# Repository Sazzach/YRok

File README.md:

## Building

To build the firmware, first download the GNU ARM toolchain from: https://developer.arm.com/open-source/gnu-toolchain/gnu-rm/downloads and extract it into the root directory for this project. Then enter the firmware directory and use Make to build the firmware.

To see a video demonstration of our final project: https://photos.app.goo.gl/VnfEDqI2edRJLxgh1

## Pinout

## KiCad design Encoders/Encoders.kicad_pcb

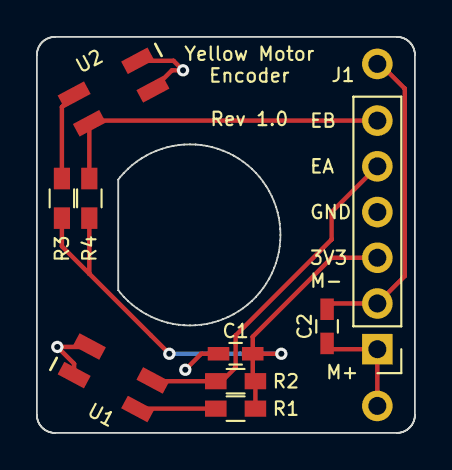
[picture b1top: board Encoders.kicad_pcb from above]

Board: 2 copper layers, 21.0 x 22.0 mm, 10 parts (0 on the bottom side), 8 nets.

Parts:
C1, C2: 0.1uF; C_0603_HandSoldering
J1: Conn_01x06; Pin_Header_Straight_1x06_Pitch2.54mm
M1: Motor; Yellow_Motor
R1, R2, R3, R4: R; R_0603_HandSoldering
U1, U2: QRE1113GR

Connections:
+3V3: C1.1, J1.3, R1.1, R2.1, R3.1, R4.1
/E_A: J1.5, R2.2, U1.3
/E_B: J1.6, R4.2, U2.3
/M+: C2.1, J1.1, M1.1
/M-: C2.2, J1.2, M1.2
GND: C1.2, J1.4, U1.1, U1.4, U2.1, U2.4
unnamed: R1.2, U1.2
unnamed: R3.2, U2.2

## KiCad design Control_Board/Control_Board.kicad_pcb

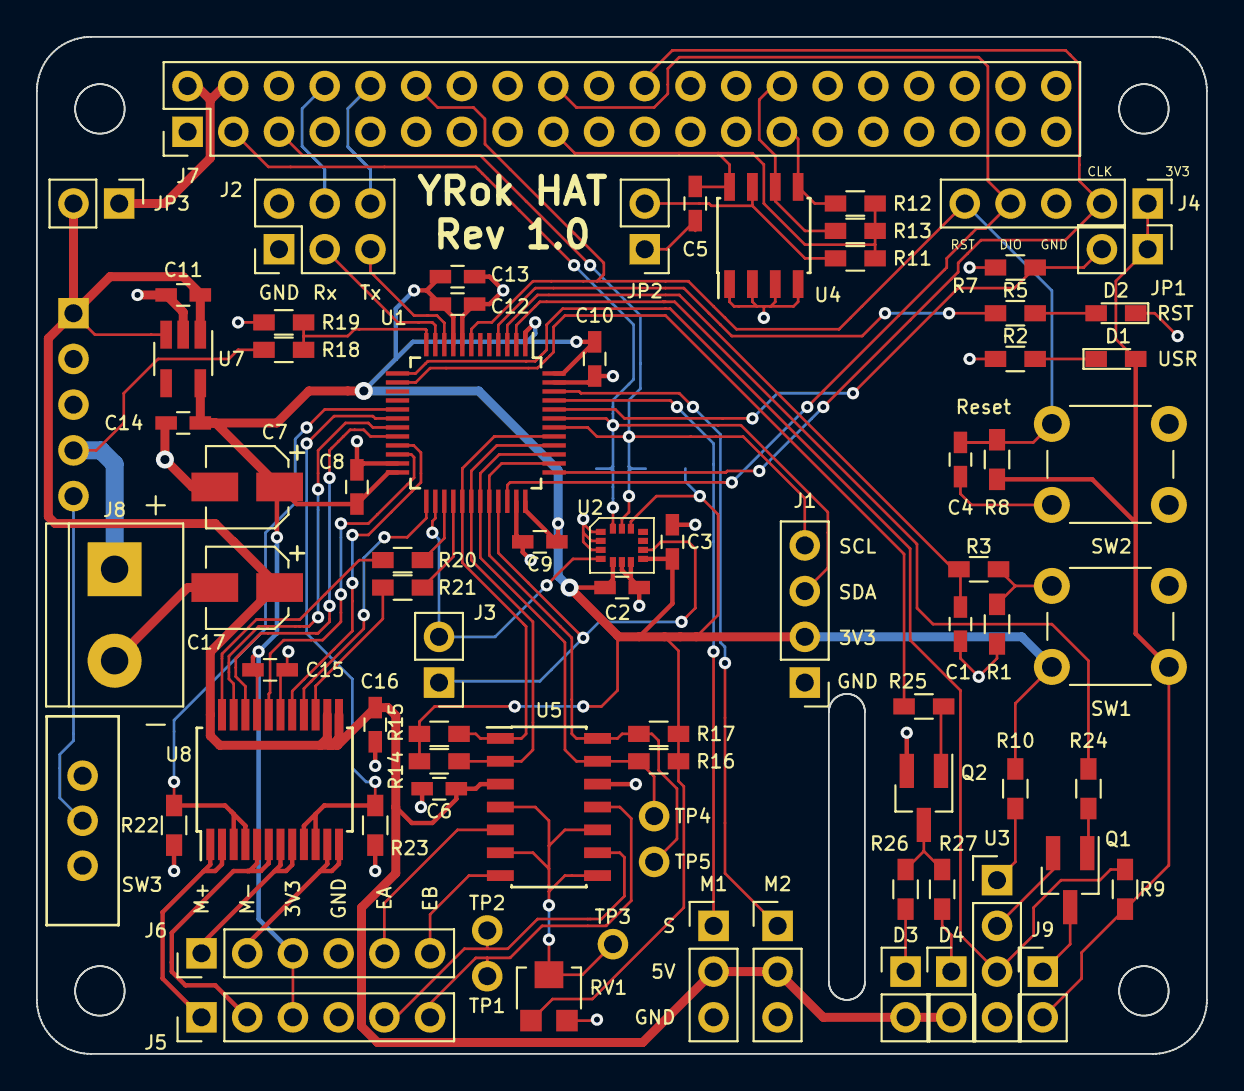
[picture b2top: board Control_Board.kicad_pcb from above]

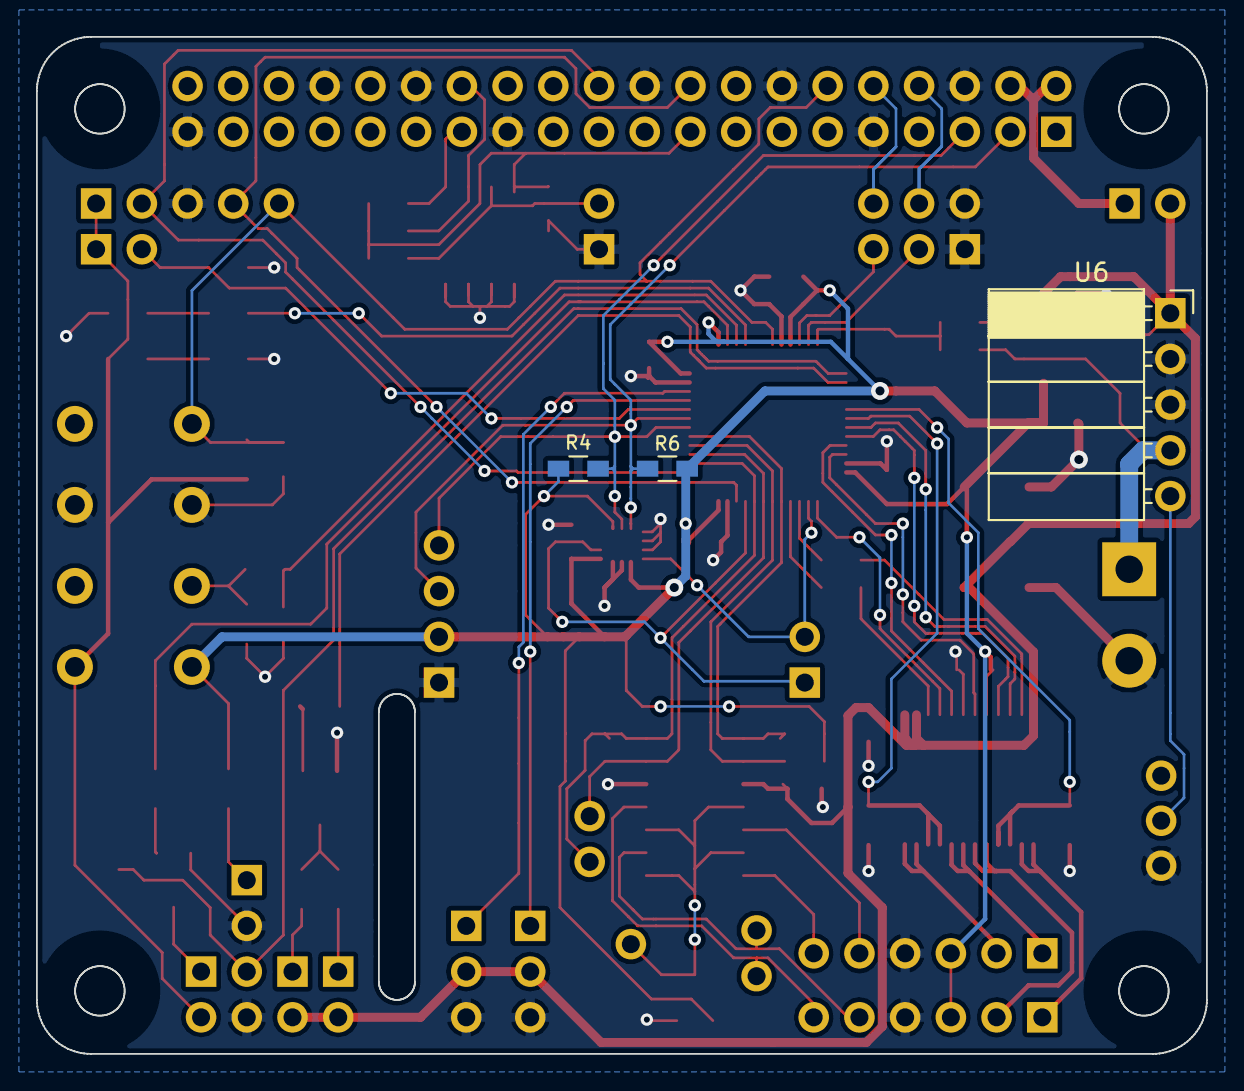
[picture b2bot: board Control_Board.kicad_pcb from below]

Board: 2 copper layers, 65.0 x 56.5 mm, 81 parts (3 on the bottom side), 64 nets.

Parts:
C1, C2, C3, C4, C5, C6, C8, C9, C10, C12, C15, C16: 0.1uF; C_0603_HandSoldering
C7: 4.7uF; CP_Elec_4x4.5
C11, C13, C14: 1uF; C_0603_HandSoldering
C17: 10uF; CP_Elec_4x4.5
D1: RED; LED_0603_HandSoldering
D2: GREEN; LED_0603_HandSoldering
D3, D4: WHITE; Pin_Header_Straight_1x02_Pitch2.54mm
J1: Breakout_A; Pin_Header_Straight_1x04_Pitch2.54mm
J2: Conn_02x03; Pin_Header_Straight_2x03_Pitch2.54mm
J3: Breakout_B; Pin_Header_Straight_1x02_Pitch2.54mm
J4: SWD; Pin_Header_Straight_1x05_Pitch2.54mm
J5: M1; Pin_Header_Straight_1x06_Pitch2.54mm
J6: M2; Pin_Header_Straight_1x06_Pitch2.54mm
J7: Raspberry_Pi_2_3; Pin_Header_Straight_2x20_Pitch2.54mm
J8: Battery - 9.6V; TerminalBlock_bornier-2_P5.08mm
J9: Laser; Pin_Header_Straight_1x02_Pitch2.54mm
JP1: J_Boot; Pin_Header_Straight_1x02_Pitch2.54mm
JP2: J_WP; Pin_Header_Straight_1x02_Pitch2.54mm
JP3: J_Pi_5V; Pin_Header_Straight_1x02_Pitch2.54mm
M1, M2: SG90; Pin_Header_Straight_1x03_Pitch2.54mm
Q1, Q2: MMBT3904; SOT-23_Handsoldering
R1, R3, R7, R8, R9: 10k; R_0603_HandSoldering
R2, R5, R24, R25: 470; R_0603_HandSoldering
R4, R6, R11, R12, R13: 3.9k; R_0603_HandSoldering
R10, R20, R21, R26, R27: 100; R_0603_HandSoldering
R14, R15, R16, R17, R19: 100k; R_0603_HandSoldering
R18: 330k; R_0603_HandSoldering
R22, R23: 0.1; R_0603_HandSoldering
RV1: POT; Pot_TC33X_2
SW1: SW_Push; SW_PUSH_6mm
SW2: SW_RST; SW_PUSH_6mm
SW3: SW_SPDT; SPDT_EG1218
TP1, TP2, TP3, TP4, TP5: Test_Point
U1: STM32F071CBT6; LQFP-48_7x7mm_Pitch0.5mm
U2: LSM6DS3
U3: QRD1114; Pin_Header_Straight_1x04_Pitch2.54mm
U4: CAT24C32; SOIC-8_3.9x4.9mm_Pitch1.27mm
U5: LM339; SOIC-14_3.9x8.7mm_Pitch1.27mm
U6: D24V50F5; Socket_Strip_Angled_1x05_Pitch2.54mm
U7: AP2127K-3.3; SOT-23-5_HandSoldering
U8: TB6612FNG; SSOP-24_5.3x8.2mm_Pitch0.65mm

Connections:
+3V3: C2.1, C3.1, C7.1, C8.1, C9.1, C10.1, C12.1, C13.1, C14.1, C15.1, D1.2, J1.2, J4.1, J5.3, J6.3, J9.2, JP1.1, R4.1, R6.1, R8.1, R9.1, R10.1, R14.1, R15.2, R16.2, R17.2, RV1.1, SW1.1, U1.1, U1.9, U1.24, U1.36, U1.48, U2.5, U2.8, U2.12, U7.5, U8.20
+5V: C6.1, C11.1, C16.1, C17.1, D3.2, D4.2, JP3.2, M1.2, M2.2, U5.3, U6.1, U7.1, U7.3, U8.13, U8.14, U8.24
/BAT_REF: R18.2, R19.1, U1.12
/E1_A: J5.5, TP2.1, U5.9
/E1_A_Cmp: R17.1, TP5.1, U1.32, U1.38, U5.14
/E1_B: J5.6, TP1.1, U5.11
/E1_B_Cmp: R16.1, TP4.1, U1.31, U1.39, U5.13
/E2_A: J6.5, U5.5
/E2_A_Cmp: R14.2, U1.30, U1.40, U5.2
/E2_B: J6.6, U5.7
/E2_B_Cmp: R15.1, U1.29, U1.41, U5.1
/INT1: J3.2, U1.26, U2.4
/INT2: J3.1, U1.33, U2.9
/LASER_EN: R24.2, U1.2
/LIGHT_EN: R25.2, U1.14
/M1+: J5.1, U8.1, U8.2
/M1-: J5.2, U8.5, U8.6
/M1_BK: U1.19, U8.22
/M1_FW: U1.20, U8.21
/M1_I: R22.1, U1.17, U8.3, U8.4
/M2+: J6.1, U8.7, U8.8
/M2-: J6.2, U8.11, U8.12
/M2_BK: U1.21, U8.17
/M2_FW: U1.25, U8.16
/M2_I: R23.1, U1.18, U8.9, U8.10
/OBJ_SENSE: R9.2, U1.13, U3.3
/PWM1: R20.2, U1.27
/PWM2: R21.2, U1.28
/Pi_RX: J2.6, J7.10
/Pi_TX: J2.4, J7.8
/Power/+9.6V: J8.1, R18.1, U6.4
/Raspberry_Pi/ID_SC: J7.28, R13.2, U4.6
/Raspberry_Pi/ID_SD: J7.27, R12.2, U4.5
/Raspberry_Pi/nRST: C4.1, J4.5, J7.12, R8.2, SW2.1, U1.7
/S1_PWM: M1.1, U1.45
/S2_PWM: M2.1, U1.46
/SCL: J1.4, J7.5, R4.2, U1.42, U2.13
/SDA: J1.3, J7.3, R6.2, U1.43, U2.14
/STBY: U1.22, U8.19
/STM_RX: J2.3, U1.11
/STM_TX: J2.5, U1.10
/SWDIO: J4.4, J7.18, U1.34
/SWD_CLK: J4.2, J7.22, U1.37
/USER_BTN: C1.1, R3.2, U1.3
/USER_LED: R5.1, U1.4
GND: C1.2, C2.2, C3.2, C4.2, C5.2, C6.2, C7.2, C8.2, C9.2, C10.2, C11.2, C12.2, C13.2, C14.2, C15.2, C16.2, C17.2, D2.1, J1.1, J2.1, J2.2, J4.3, J5.4, J6.4, J7.6, J7.9, J7.14, J7.20, J7.25, J7.30, J7.34, J7.39, J8.2, JP2.1, M1.3, M2.3, Q1.2, Q2.2, R1.2, R2.2, R7.2, R19.2, R22.2, R23.2, RV1.3, SW2.2, SW3.1, U1.8, U1.23, U1.35, U1.47, U2.1, U2.2, U2.3, U2.6, U2.7, U3.2, U3.4, U4.1, U4.2, U4.3, U4.4, U5.12, U6.2, U6.3, U7.2, U8.18
unnamed: C5.1, J7.17, R11.1, R12.1, R13.1, U4.8
unnamed: D1.1, R2.1
unnamed: D2.2, R5.2
unnamed: D3.1, R26.1
unnamed: D4.1, R27.1
unnamed: J7.2, J7.4, JP3.1
unnamed: J9.1, Q1.3
unnamed: JP1.2, R7.1, U1.44
unnamed: JP2.2, R11.2, U4.7
unnamed: Q1.1, R24.1
unnamed: Q2.1, R25.1
unnamed: Q2.3, R26.2, R27.2
unnamed: R1.1, R3.1, SW1.2
unnamed: R10.2, U3.1
unnamed: R20.1, U8.23
unnamed: R21.1, U8.15
unnamed: RV1.2, TP3.1, U5.4, U5.6, U5.8, U5.10
unnamed: SW3.2, U6.5

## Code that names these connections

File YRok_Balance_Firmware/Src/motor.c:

#include "motor.h"

uint32_t M1_FW = 1;
uint32_t M1_BK = 2;
uint32_t M2_FW = 12;
uint32_t STBY = 11;
uint32_t M2_BK = 10;
uint32_t M1_PWM = 14;
uint32_t M2_PWM = 15;

// Set up gpio and timers for motors.
void init_motors()
{
  RCC->AHBENR |= RCC_AHBENR_GPIOAEN | RCC_AHBENR_GPIOBEN;
  //RCC->APB1ENR |= RCC_APB1ENR_TIM2EN | RCC_APB1ENR_TIM3EN;
  RCC->APB2ENR |= RCC_APB2ENR_TIM15EN;

  //GPIOA->MODER |= (0x2 << 15*2); // E1_A

  //GPIOA->AFR[2] |= (0x2 << (15 - 8)*4);

  GPIOB->MODER |= (0x1 << M1_BK*2) | // M1_BK
                  (0x1 << M1_FW*2) | // M1_FW
                  (0x1 << M2_BK*2) | // M2_BK
                  (0x1 << STBY*2) | // STBY
                  (0x1 << M2_FW*2) | // M2_FW
                  (0x2 << M1_PWM*2) | // M1_PWM
                  (0x2 << M2_PWM*2); // M2_PWM
                  //(0x2 << 3*2); // E1_B
                  //(0x2 << 4*2) | // E2_A
                  //(0x2 << 5*2); // E2_B

  //GPIOB->AFR[0] |= (0x2 << 3*4) | (0x1 << 4*4) | (0x1 << 5*4);
  //GPIOB->AFR[0] |= (0x2 << 3*4);
  GPIOB->AFR[1] |= (0x1 << (M1_PWM - 8)*4) |(0x1 << (M2_PWM - 8)*4);

  // Select PWM mode 1, and enable OC1 preload register
  TIM15->CCMR1 |= TIM_CCMR1_OC1M_2 | TIM_CCMR1_OC1M_1 | TIM_CCMR1_OC1PE |
                  TIM_CCMR1_OC2M_2 | TIM_CCMR1_OC2M_1 | TIM_CCMR1_OC2PE;
  TIM15->CCER |= TIM_CCER_CC1E |
                 TIM_CCER_CC2E;
  TIM15->BDTR |= TIM_BDTR_MOE;
  TIM15->PSC = 0;
  TIM15->ARR = 2400; // PWM at 20kHz (Clock is 48MHz)
  TIM15->CCR1 = 0;
  TIM15->CCR2 = 0;

  // Start timer
  TIM15->CR1 |= TIM_CR1_CEN;

//  // Setup timer 2 (E1)
//  TIM2->CCMR1 |= (TIM_CCMR1_CC1S_0 | TIM_CCMR1_CC2S_0);
//  TIM2->SMCR |= (TIM_SMCR_SMS_1 | TIM_SMCR_SMS_0);
//  TIM2->CCER |= (TIM_CCER_CC1E | TIM_CCER_CC2E);
//  TIM2->ARR = 0xFFFF;
//  TIM2->CNT = 0x7FFF;
//  TIM2->CR1 |= TIM_CR1_CEN;
//
//  // Setup timer 3 (E2)
//  TIM3->CCMR1 |= (TIM_CCMR1_CC1S_0 | TIM_CCMR1_CC2S_0);
//  TIM3->SMCR |= (TIM_SMCR_SMS_1 | TIM_SMCR_SMS_0);
//  TIM3->ARR = 0xFFFF;
//  TIM3->CNT = 0x7FFF;
//  TIM3->CR1 |= TIM_CR1_CEN;
}

// Enable the standby pin on the h-bridge.
void enable_motors()
{
  GPIOB->ODR |= (0x1 << STBY);
}

// Disable the standby pin on the h-bridge.
void disable_motors()
{
  GPIOB->ODR &= ~(0x1 << STBY);
}

// Set the direction of the motor
void set_dir(int32_t motor, int32_t dir)
{
  uint32_t fw_pin = M1_FW;
  uint32_t bk_pin = M1_BK;

  if(motor == 2)
  {
    fw_pin = M2_FW;
    bk_pin = M2_BK;
  }

  switch(dir)
  {
    case MOTOR_STOP:
      GPIOB->ODR &= ~((0x1 << fw_pin) | (0x1 << bk_pin));
      break;
    case MOTOR_FORWARD:
      GPIOB->ODR |= (0x1 << fw_pin);
      GPIOB->ODR &= ~(0x1 << bk_pin);
      break;
    case MOTOR_BACKWARD:
      GPIOB->ODR |= (0x1 << bk_pin);
      GPIOB->ODR &= ~(0x1 << fw_pin);
      break;
  }
}

// Set the speed of the motor
void set_speed(int32_t motor, int32_t speed)
{
  if(speed > 0) {
    set_dir(motor, MOTOR_FORWARD);
  }
  else {
    set_dir(motor, MOTOR_BACKWARD);
    speed = -speed;
  }

  if(speed > 100) {
    speed = 100;
  }

  uint32_t tim_speed = (TIM15->ARR / 100) * speed;

  if(motor == 1)
  {
    TIM15->CCR1 = tim_speed;
  }
  else if(motor == 2)
  {
    TIM15->CCR2 = tim_speed;
  }
}

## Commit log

2018-03-29 Added a readme and basic documentation.
2018-03-29 Added Kicad files, and chassis files.
2018-03-29 Removed irrelevant chassis files, got newer copies of others.
2018-04-09 Added openocd configuration file.
2018-04-10 Updated chassis, added Control Board Schematic, and added led blinking to firmware.
2018-04-11 Added tabs and captive bolts.
2018-04-11 Added basic motor init.
2018-04-12 Chassis is 99% done, just needs dimension checking.
2018-04-18 Got uart echo working
2018-04-18 Encoders working with hal. Some issues with extra counts sometimes.
2018-04-18 Added the IMU control .c and .h files
2018-04-18 added newlines to uart
2018-04-18 made small changes for who_am_i imu
2018-04-18 Should transmit the contents of the who_am_i register now
2018-04-18 IMU should be working now, but haven't been able to check
2018-04-20 ljdf
2018-04-20 Who_am_i sanity checks and reading one byte of XAccel
2018-04-20 Able to get the x of the accelerometer using function get_ax
2018-04-20 ldjf
2018-04-21 Now can also read the two bytes for the Gyroscope's Y
2018-04-21 Crappy PI
2018-04-21 Added some gyro stuff to pid.
2018-04-21 fusion
2018-04-21 Semi working
2018-04-22 got it workinggit add -A!
2018-04-23 First working version!
2018-04-25 added command parsing
2018-04-25 Balance, and orientation control.
2018-04-26 Final Chassis
2018-04-27 ldfj
2018-04-27 dlfj
2018-04-27 Added comments.
